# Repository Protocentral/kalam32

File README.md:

# ProtoCentral Kalam32-Dev ESP32 Wi-Fi and Bluetooth IoT platform
-------------------

[!
Dont have it yet? But one here: ProtoCentral Kalam32-Dev ESP32 Wi-Fi and Bluetooth IoT platform](https://www.protocentral.com/kalam-iot/1156-protocentral-kalam32-dev-esp32-wi-fi-and-bluetooth-iot-platform.html)

Meet the Espressif ESP32, a much-awaited sequel of the very popular ESP8266 SoC. This time around Espressif has given it a ton of integrated feature-rich peripherals. The CPU(s) is also upgraded with two individual cores from Tensilica, each running at up to 240 MHz. Two because one takes care of the Wi-Fi and Bluetooth stacks' computational requirements and the other one dedicated for the application.

This is just a lot of power waiting to be unleashed and still works on very low power for IoT applications. We are very excited with the capability of this chip and waiting to find more applications for it.

At the time of writing this document, the support for ESP32 in Arduino is still kind of patchy, however Espressif has an excellent development toolchain based on the Xtensa toolchain for Tensilica controllers. We love using Epressif's ESP-IDF toolchain and framework, it includes a great set of libraries. It works on Windows, MACOS and Linux. We use it on Ubuntu and it works like a charm.

Note: This product is still undergoing complete software testing for the various capabilities. Watch this page for more updates as we keep adding features in software for this.

Note: The Arduino core for ESP32 is still under development, so with the current state of the software, this board may not be a drop-in replacement for an Arduino. This feature should be available soon though.

##Features:

* On-board ESP32 System-On-Chip (SoC) featuring:
* Two Tensilica LX6 microcontroller cores running at 240 MHz, with 520 KB RAM !!
* Integrated Wi-Fi controller (802.11 b/g/n/i) up to 150 Mbps
* Integrated Dual-mode Bluetooth 4.2 controller ("classic" and Bluetooth low * energy (BLE) support)
* 12-bit SAR 12-channel ADC
* 8-bit, 2-channel DAC
* Capacitive touch sensor interface
* LED PWM controller
* CAN 2.0 controller
* Integrated temperature sensor
* Integrated Hall-effect sensor 
* Operating temperature range: -40 C to +125 C
* 4 MB on-board FLASH memory
* On-board 2.4 GHz PCB trace antenna for Wi-Fi/Bluetooth
* On-board FTDI FT231X USB-UART converter
* Operation from single Li-Poly battery with on-board charger and regulator
* 2x capacitive touch switches
* 3x WS2812B addressable RGB LEDs
* Arduino Uno compatible form-factor for addition of shields

Repository Contents
-------------------
* **/hardware** - All Eagle design files (.brd, .sch)
* **/docs** - Additional Documentation

License Information
-------------------
This product is open source!

Please use, reuse, and modify these files as you see fit. Please maintain attribution to Protocentral and release anything derivative under the same license.

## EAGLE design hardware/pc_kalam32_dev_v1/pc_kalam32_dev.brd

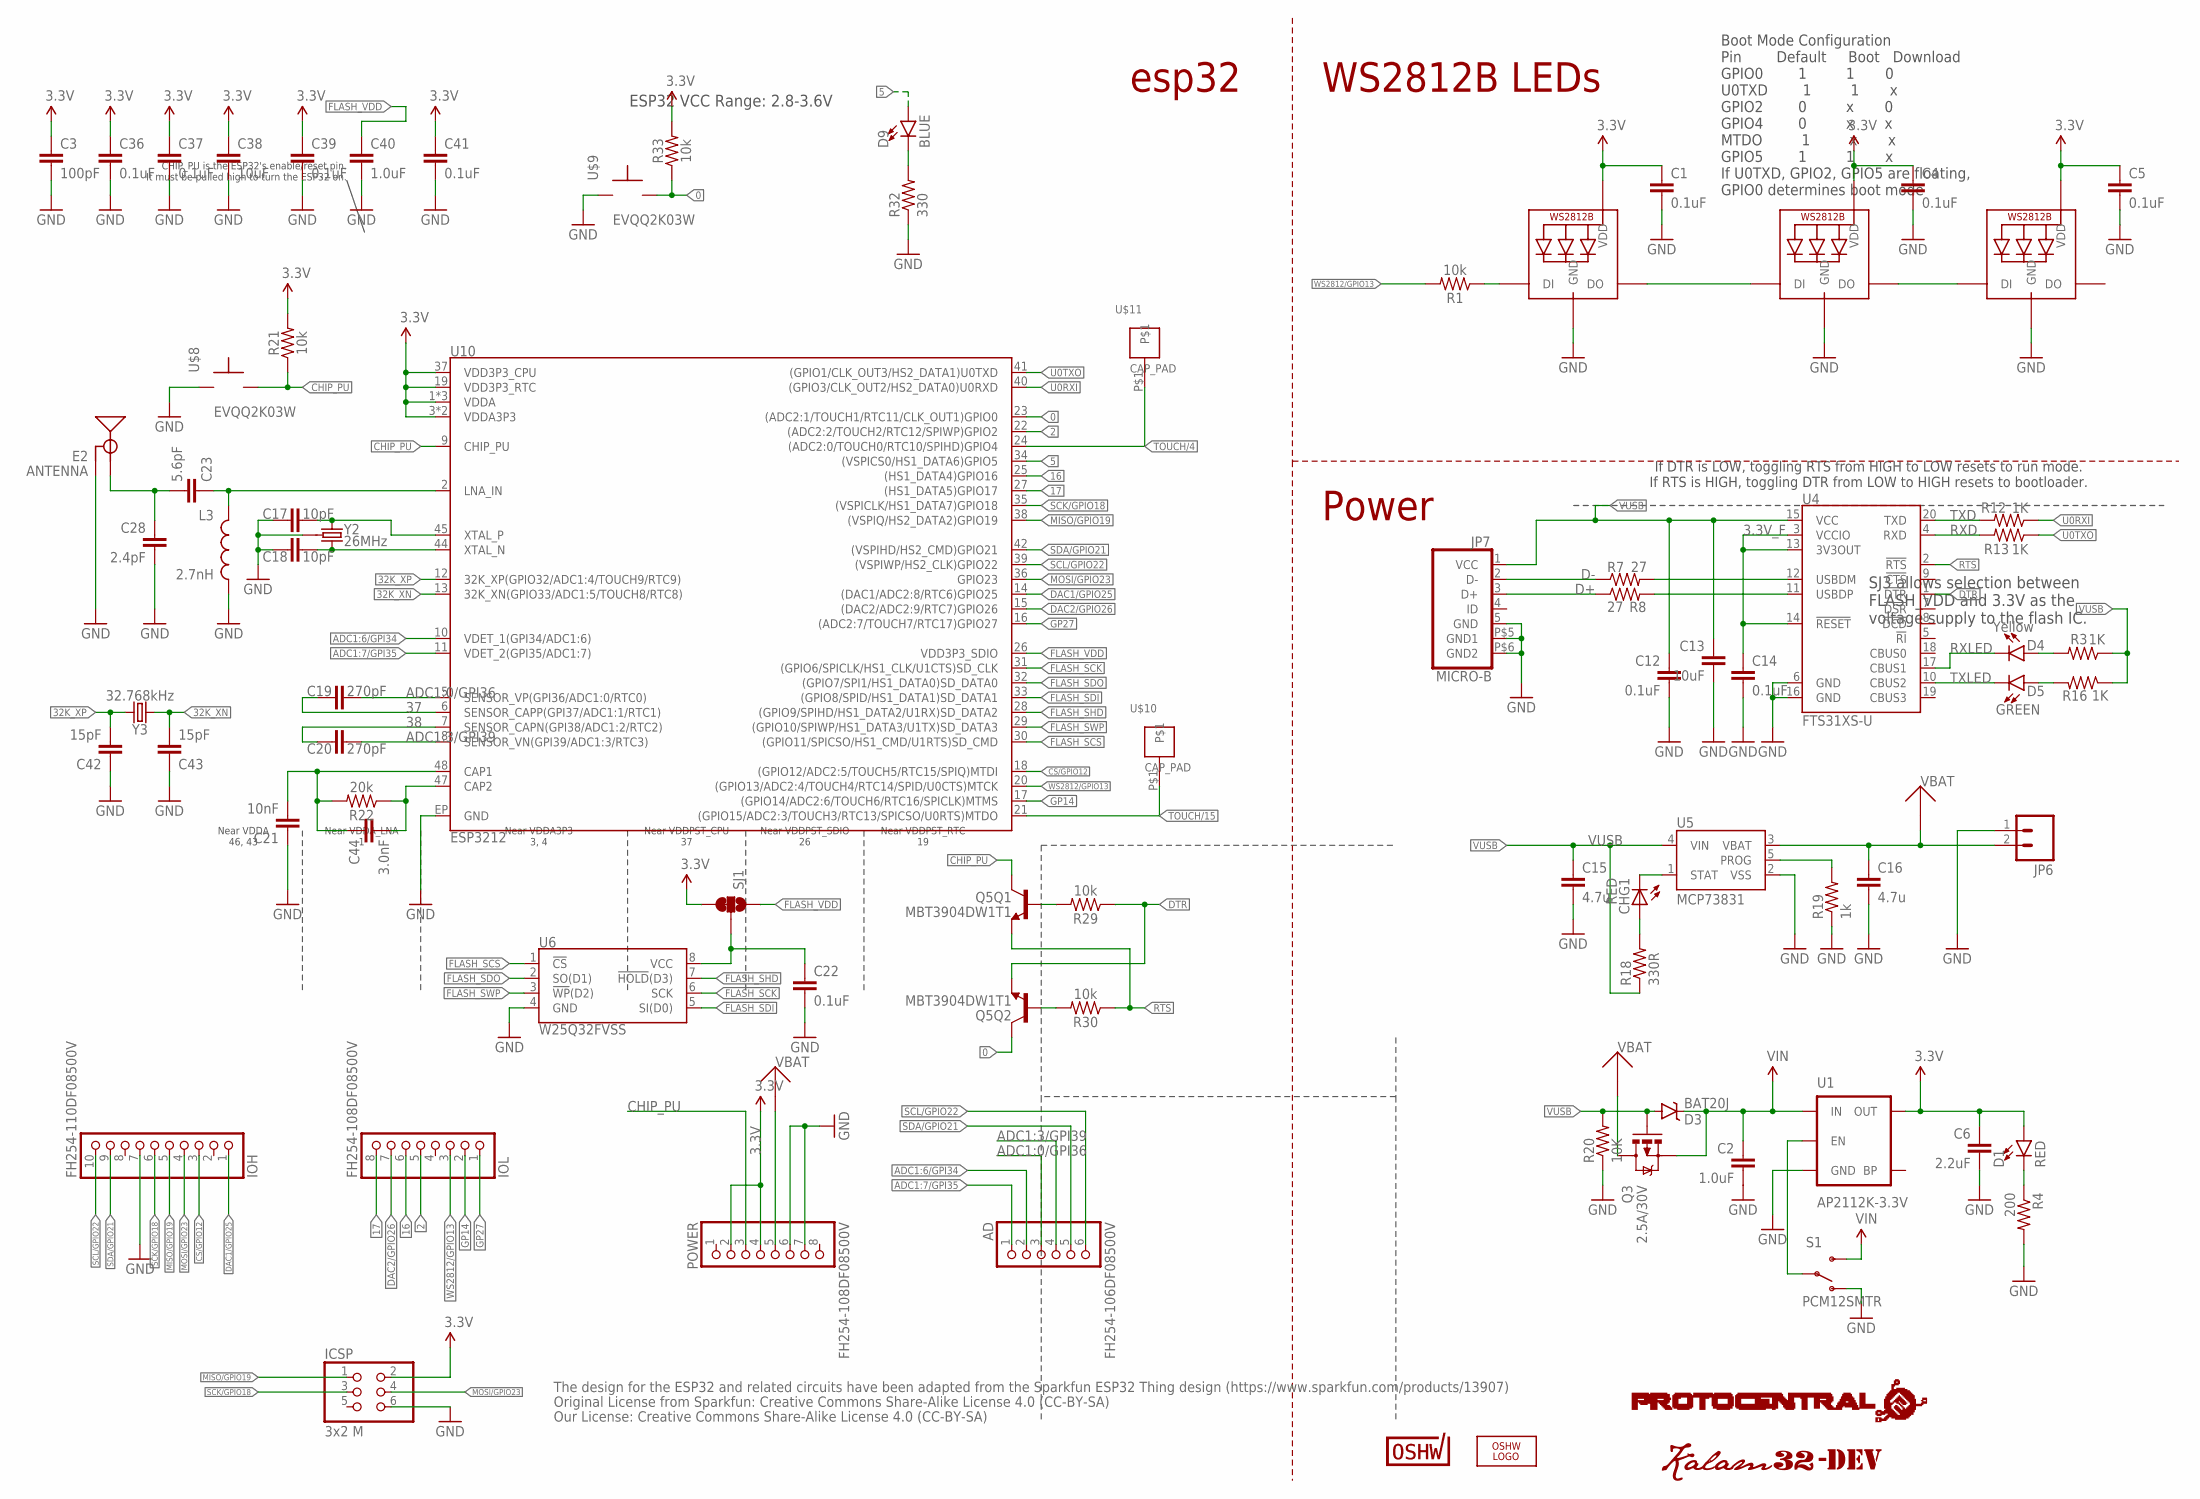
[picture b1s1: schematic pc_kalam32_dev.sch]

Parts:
AD: FH254-106DF08500V; 1X06
C1, C4, C5, C22, C36, C37, C39, C41: 0.1uF; 0603
C2: 1.0uF; C0402
C3: 100pF; 0603
C6: 2.2uF; 0603-CAP@1
C12, C14: 0.1uF; C0402
C13: 10uF; C0805
C15, C16: 4.7u; C0805
C17, C18: 10pF; 0603
C19, C20: 270pF; 0603
C21: 10nF; 0603
C23: 5.6pF; 0603
C28: 2.4pF; 0603
C38: 10uF; 0603
C40: 1.0uF; 0603
C42, C43: 15pF; 0603
C44: 3.0nF; 0603
CHG1: RED; CHIPLED_0603
D1: RED; LED-0603
D3: BAT20J; SOD-323
D4: Yellow; LED-0603
D5: GREEN; LED-0603@1
D9: BLUE; LED-0603
E2: ANTENNA; TRACE_ANTENNA_2.4GHZ_25.7MM_TUNED
ICSP: 3x2 M; 2X03
IOH: FH254-110DF08500V; 1X10
IOL: FH254-108DF08500V; 1X08
JP6: M02-JST-2MM-SMT; JST-2-SMD
JP7: MICRO-B
L3: 2.7nH; 0603
LED1, LED2, LED3: WS2812B5050; WS2812B
LOGO2: OSHW_LOGO_FILLX0200-NT; OSHW_FILLX200_NOTEXT
POWER: FH254-108DF08500V; 1X08
Q3: 2.5A/30V; SOT23-3
Q5: MBT3904DW1T1; SC70-6
R1, R21, R29, R30, R33: 10k; 0603
R3, R12, R13, R16: 1K; R0402
R4: 200; R0402
R7, R8: 27; R0402
R18: 330R; R0402
R19: 1k; R0402
R20: 10K; R0402
R22: 20k; 0603
R32: 330; R0805
S1: PCM12SMTR; SWITCH-SPST-SMD-A
SJ1: JUMPER-PAD-3-2OF3_NC_BY_TRACE_SMALL; PAD-JUMPER-3-2OF3_NC_BY_TRACE_YES_SILK_FULL_BOX
U1: AP2112K-3.3V; SOT23-5
U4: FTS31XS-U; SSOP20_L
U5: MCP73831; SOT23-5
U6: W25Q32FVSS; SOIC-8
U10: ESP3212; QFN48-0.4MM
U$5: CERT-MEDIUM; CERT-MED-SILK
U$8, U$9: EVQQ2K03W; EVQQ2
U$10, U$11: CAP_PAD
U$12: KALAM32-DEV
U$13: PROTY_LOGO_WITH_TEXT; PROTY_WITH_TEXT
Y2: 26MHz; CRYSTAL-SMD-3.2X2.5
Y3: 32.768kHz; CRYSTAL-SMD-3.2X1.5MM

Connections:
0: Q5.6 (C), R33.1, U10.23 ((ADC2:1/TOUCH1/RTC11/CLK_OUT1)GPIO0), U$9.P$3
2: IOL.5, U10.22 ((ADC2:2/TOUCH2/RTC12/SPIWP)GPIO2)
3.3V: C1.1, C3.1, C4.1, C5.1, C6.1, C36.1, C37.1, C38.1, C39.1, C41.1, D1.A, ICSP.2, LED1.1-VDD (VDD), LED2.1-VDD (VDD), LED3.1-VDD (VDD), POWER.2, POWER.4, R21.2, R33.2, SJ1.3, U1.5 (OUT), U10.1 (VDDA), U10.3 (VDDA3P3), U10.4 (VDDA3P3), U10.19 (VDD3P3_RTC), U10.37 (VDD3P3_CPU), U10.43 (VDDA), U10.46 (VDDA)
3.3V_F: C14.1, U4.3 (VCCIO), U4.13 (3V3OUT), U4.14 (!RESET)
5: D9.A, U10.34 ((VSPICS0/HS1_DATA6)GPIO5)
16: IOL.6, U10.25 ((HS1_DATA4)GPIO16)
17: IOL.8, U10.27 ((HS1_DATA5)GPIO17)
32K_XN: C43.2, U10.13 (32K_XN(GPIO33/ADC1:5/TOUCH8/RTC8)), Y3.P$2 (2)
32K_XP: C42.2, U10.12 (32K_XP(GPIO32/ADC1:4/TOUCH9/RTC9)), Y3.P$1 (1)
37: C19.1, U10.6 (SENSOR_CAPP(GPI37/ADC1:1/RTC1))
38: C20.1, U10.7 (SENSOR_CAPN(GPI38/ADC1:2/RTC2))
ADC1:0/GPI36: AD.3, C19.2, U10.5 (SENSOR_VP(GPI36/ADC1:0/RTC0))
ADC1:3/GPI39: AD.4, C20.2, U10.8 (SENSOR_VN(GPI39/ADC1:3/RTC3))
ADC1:6/GPI34: AD.2, U10.10 (VDET_1(GPI34/ADC1:6))
ADC1:7/GPI35: AD.1, U10.11 (VDET_2(GPI35/ADC1:7))
CAP_10N: C21.2, C44.1, R22.2, U10.48 (CAP1)
CHIP_PU: POWER.3, Q5.3 (C), R21.1, U10.9 (CHIP_PU), U$8.P$3
CS/GPIO12: IOH.3, U10.18 ((GPIO12/ADC2:5/TOUCH5/RTC15/SPIQ)MTDI)
D+: JP7.3 (D+), R8.1
D-: JP7.2 (D-), R7.1
DAC1/GPIO25: IOH.1, U10.14 ((DAC1/ADC2:8/RTC6)GPIO25)
DAC2/GPIO26: IOL.7, U10.15 ((DAC2/ADC2:9/RTC7)GPIO26)
DTR: Q5.1 (E), R29.1, U4.1 (!DTR)
FLASH_SCK: U6.6 (SCK), U10.31 ((GPIO6/SPICLK/HS1_CLK/U1CTS)SD_CLK)
FLASH_SCS: U6.1 (!CS!), U10.30 ((GPIO11/SPICSO/HS1_CMD/U1RTS)SD_CMD)
FLASH_SDI: U6.5 (SI(D0)), U10.33 ((GPIO8/SPID/HS1_DATA1)SD_DATA1)
FLASH_SDO: U6.2 (SO(D1)), U10.32 ((GPIO7/SPI1/HS1_DATA0)SD_DATA0)
FLASH_SHD: U6.7 (!HOLD!(D3)), U10.28 ((GPIO9/SPIHD/HS1_DATA2/U1RX)SD_DATA2)
FLASH_SWP: U6.3 (!WP!(D2)), U10.29 ((GPIO10/SPIWP/HS1_DATA3/U1TX)SD_DATA3)
FLASH_VDD: C40.1, SJ1.1, U10.26 (VDD3P3_SDIO)
GND: C1.2, C2.2, C3.2, C4.2, C5.2, C6.2, C12.2, C13.2, C14.2, C15.2, C16.2, C17.1, C18.1, C21.1, C22.2, C28.2, C36.2, C37.2, C38.2, C39.2, C40.2, C41.2, C42.1, C43.1, E2.GND, E2.GND2 (GND), ICSP.6, IOH.7, JP6.1, JP7.5 (GND), JP7.P$5 (GND1), JP7.P$6 (GND2), L3.2, LED1.3-GND (GND), LED2.3-GND (GND), LED3.3-GND (GND), POWER.6, POWER.7, R4.2, R19.1, R20.1, R32.1, S1.1 (O), U1.2 (GND), U4.6 (GND), U4.16 (GND), U5.2 (VSS), U6.4 (GND), U10.EP (GND), U$8.P$1, U$9.P$1, Y2.2 (GND), Y2.4 (GND)
GP14: IOL.2, U10.17 ((GPIO14/ADC2:6/TOUCH6/RTC16/SPICLK)MTMS)
GP27: IOL.1, U10.16 ((ADC2:7/TOUCH7/RTC17)GPIO27)
LNA_IN: C23.1, L3.1, U10.2 (LNA_IN)
MISO/GPIO19: ICSP.1, IOH.5, U10.38 ((VSPIQ/HS2_DATA2)GPIO19)
MOSI/GPIO23: ICSP.4, IOH.4, U10.36 (GPIO23)
unnamed: LED1.2-DOUT (DO), LED2.4-DIN (DI)
unnamed: LED2.2-DOUT (DO), LED3.4-DIN (DI)
unnamed: LED1.4-DIN (DI), R1.1
unnamed: D5.A, R16.2
unnamed: R7.2, U4.12 (USBDM)
unnamed: D4.A, R3.2
unnamed: R8.2, U4.11 (USBDP)
unnamed: D1.C, R4.1
unnamed: CHG1.C, U5.1 (STAT)
unnamed: S1.2, U1.3 (EN)
unnamed: CHG1.A, R18.2
unnamed: C22.1, SJ1.2, U6.8 (VCC)
unnamed: R19.2, U5.5 (PROG)
unnamed: Q5.5 (B), R29.2
unnamed: Q5.2 (B), R30.2
unnamed: C17.2, U10.45 (XTAL_P), Y2.1
unnamed: C18.2, U10.44 (XTAL_N), Y2.3 (2)
unnamed: D9.C, R32.2
unnamed: C44.2, R22.1, U10.47 (CAP2)
RTS: Q5.4 (E), R30.1, U4.2 (!RTS)
RXD: R13.2, U4.4 (RXD)
RXLED: D4.C, U4.17 (CBUS1)
SCK/GPIO18: ICSP.3, IOH.6, U10.35 ((VSPICLK/HS1_DATA7)GPIO18)
SCL/GPIO22: AD.6, IOH.10, U10.39 ((VSPIWP/HS2_CLK)GPIO22)
SDA/GPIO21: AD.5, IOH.9, U10.42 ((VSPIHD/HS2_CMD)GPIO21)
TOUCH/4: U10.24 ((ADC2:0/TOUCH0/RTC10/SPIHD)GPIO4), U$11.P$1
TOUCH/15: U10.21 ((GPIO15/ADC2:3/TOUCH3/RTC13/SPICSO/U0RT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), U$10.P$1
TRACE_ANT1: C23.2, C28.1, E2.ANT (SIGNAL)
TXD: R12.2, U4.20 (TXD)
TXLED: D5.C, U4.10 (CBUS2)
U0RXI: R12.1, U10.40 ((GPIO3/CLK_OUT2/HS2_DATA0)U0RXD)
U0TXO: R13.1, U10.41 ((GPIO1/CLK_OUT3/HS2_DATA1)U0TXD)
VBAT: C16.1, JP6.2, POWER.5, Q3.3 (D), U5.3 (VBAT)
VIN: C2.1, D3.C, Q3.2 (S), S1.3 (S), U1.1 (IN)
VUSB: C12.1, C13.1, C15.1, D3.A, JP7.1 (VCC), Q3.1 (G), R3.1, R16.1, R18.1, R20.2, U4.15 (VCC), U5.4 (VIN)
WS2812/GPIO13: IOL.3, R1.2, U10.20 ((GPIO13/ADC2:4/TOUCH4/RTC14/SPID/U0CTS)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)

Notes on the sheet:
Boot Mode Configuration Pin Default Boot Download GPIO0 1 1 0 U0TXD 1 1 x GPIO2 0 x 0 GPIO4 0 x x MTDO 1 x x GPIO5 1 1 x If U0TXD, GPIO2, GPIO5 are floating, GPIO0 determines boot mode
Near VDDA 46, 43
Near VDDA_LNA 1
Near VDDA3P3 3, 4
Near VDDPST_CPU 37
Near VDDPST_SDIO 26
Near VDDPST_RTC 19
ESP32 VCC Range: 2.8-3.6V
SJ3 allows selection between FLASH_VDD and 3.3V as the voltage supply to the flash IC.
If DTR is LOW, toggling RTS from HIGH to LOW resets to run mode. If RTS is HIGH, toggling DTR from LOW to HIGH resets to bootloader.
CHIP_PU is the ESP32's enable/reset pin. It must be pulled high to turn the ESP32 on.
esp32
The design for the ESP32 and related circuits have been adapted from the Sparkfun ESP32 Thing design (https://www.sparkfun.com/products/13907)
Original License from Sparkfun: Creative Commons Share-Alike License 4.0 (CC-BY-SA)
Our License: Creative Commons Share-Alike License 4.0 (CC-BY-SA)
WS2812B LEDs
Power

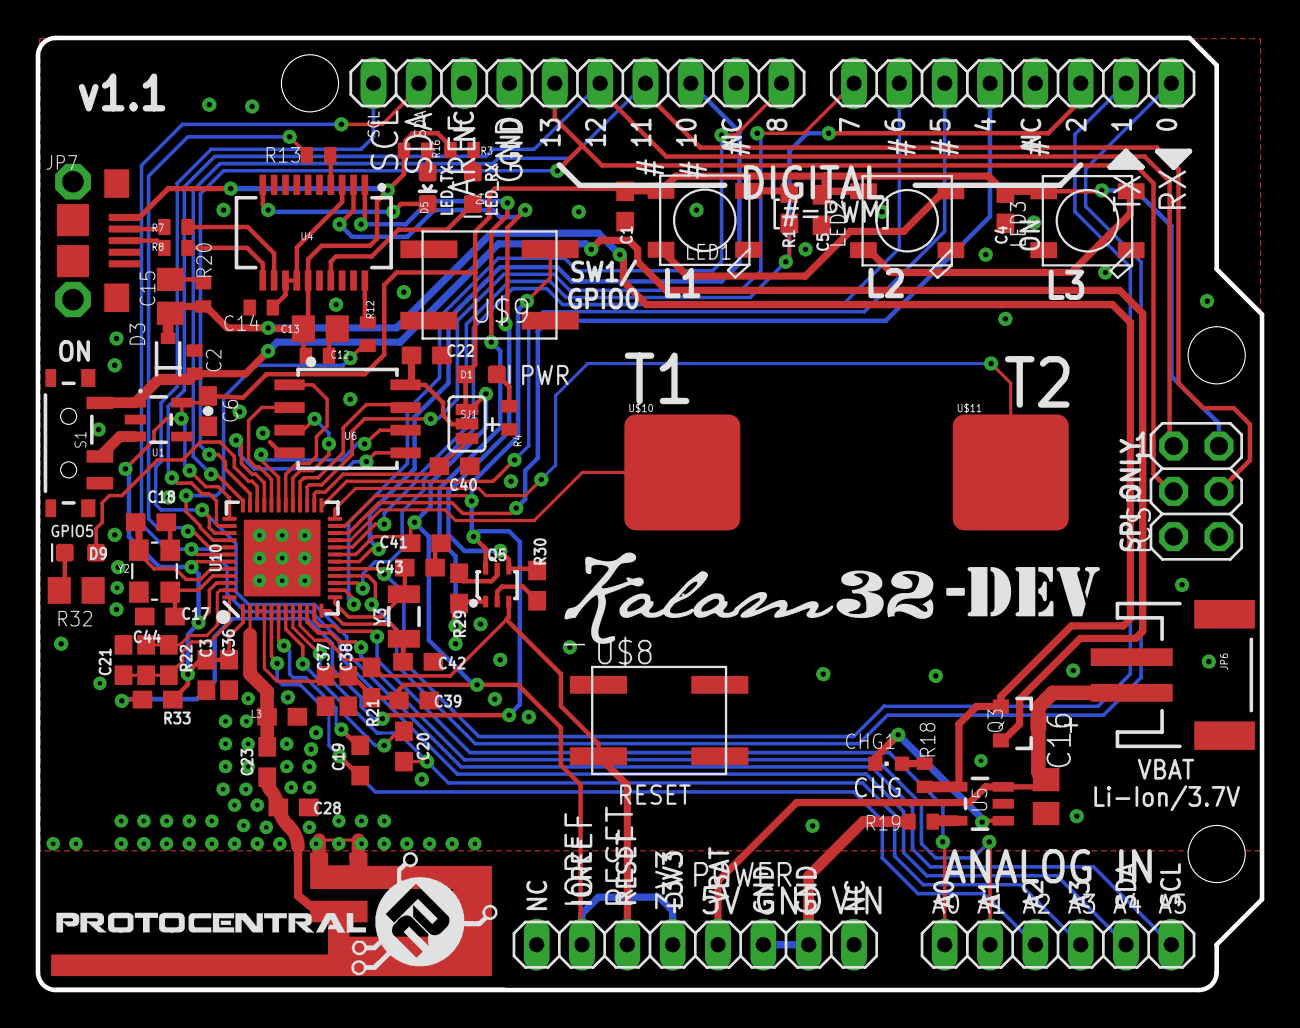
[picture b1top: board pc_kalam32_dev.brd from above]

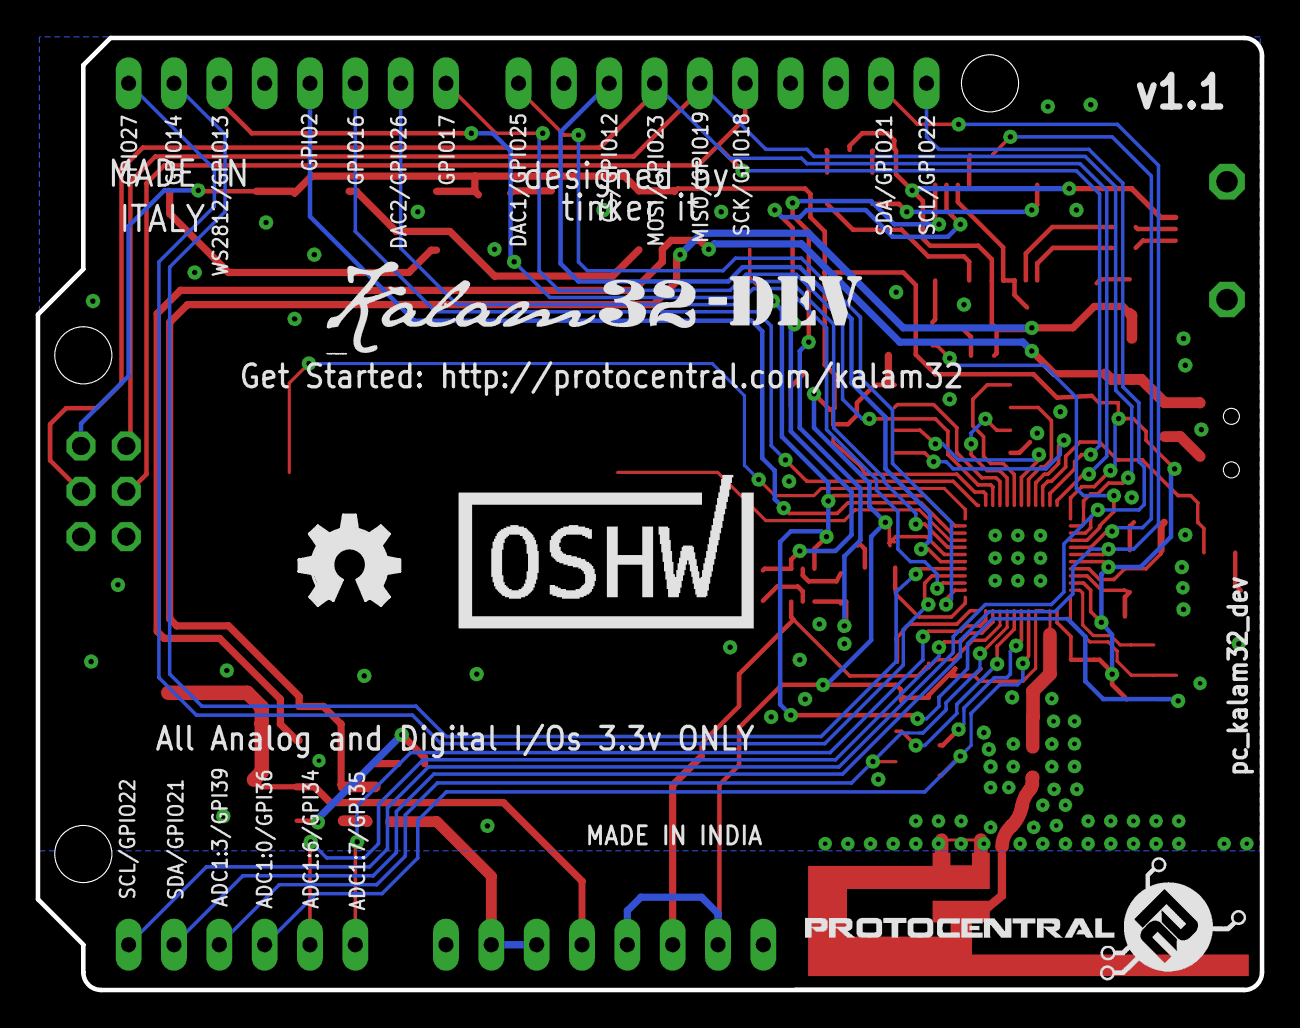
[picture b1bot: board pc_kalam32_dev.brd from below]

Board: 4 copper layers, 68.6 x 53.3 mm, 84 parts (4 on the bottom side), 72 nets.

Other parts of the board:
U$1: KALAM32-DEV
U$2: PROTY_LOGO_WITH_TEXT; PROTY_WITH_TEXT

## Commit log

2017-03-31 Updated hardware files
2017-04-01 Updated schematics
2017-04-22 Added Kalam32-DEV example for ADS1292R shield
2017-07-03 added design file for v1.1
2018-04-26 Create Example_Wifi_Test
2018-04-26 Rename Example_Wifi_Test to Example_Wifi_Test.ino

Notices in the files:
parts and their libraries:
SparkFun-Capacitors: Licensing: Creative Commons ShareAlike 4.0 International - https://creativecommons.org/licenses/by-sa/4.0
SparkFun-DigitalIC: Licensing: CC v3.0 Share-Alike You are welcome to use this library for commercial purposes.
